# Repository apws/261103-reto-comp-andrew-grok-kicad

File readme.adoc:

= Z80 simple computer
:toc:
:toclevels: 2

The schematic is the rebuilt sheet. It opens, it uses stock KiCad 10.0.7 symbols, and the parts now sit inside the paper. The notes under `docs/` say how that was done.

The PCB file in this directory is not the posted board. That file would not open, and it is kept unchanged in `as-posted/`. The project board is a new KiCad 10 board. The signal tracks from the first routing attempt have been removed. What is on it now is the Eurocard outline, the parts placed on the top, four layers, and the inner ground and +5V planes. The DE9 plug hangs off the left edge. The screw-terminal holes hang off the right edge. There are no signal tracks. The STEP models are in `libs/kicad-packages3D-10.0.7/`, and the board names them with `${KIPRJMOD}`, the project directory.

The choices for this trial are in the plan. The sheet is A3, because the DIP-40 symbols do not fit A4. The board is a 160 by 100 mm Eurocard, four layers, a screw terminal for +5V, four M3 holes, and tracks written into the board file. FreeRouting was not used.

What is left:

. Route the signals in KiCad, one group of nets at a time. Not with the 0.25 mm grid script.
. The first proposed group is the two clocks and reset. See the note on Andrew's brief.

`tools/build_schematic.py` rewrites the schematic. If you move a part in KiCad and then run that script, the script wins. Either edit in KiCad and stop using the script, or change the script. Do not do both.

Read these first:

* link:docs/261103-what-went-wrong-and-how-to-do-it.adoc[Why the posted files are not a computer]
* link:docs/261103-a-guide-for-andrew.adoc[Doing the sheet one step at a time]
* link:docs/261104-00%20Chat%20transcript%20--%20fitting%20the%20symbols%20inside%20the%20frame.adoc[Fitting the symbols inside the frame]
* link:docs/261104-01%20Plan%20--%20placing%20and%20routing%20the%20board.adoc[Plan for placing and routing the board]
* link:docs/261104-02%20Chat%20transcript%20--%20the%20board%20plan%20and%20the%20public%20repo.adoc[The board plan, and the public repository]
* link:docs/261105-22%20Placing%20the%20Eurocard%20and%20the%20first%20tracks.adoc[Placing the Eurocard, and the first tracks]
* link:docs/261105-22%20JLCPCB%20rules%20for%20this%20board.adoc[JLCPCB rules for this board]
* link:docs/261105-23%20Placement%20only,%20connectors%20facing%20out.adoc[Placement only, connectors facing out]
* link:docs/261105-23%203D%20models%20for%20the%20footprints.adoc[3D models for the footprints]
* link:docs/261106-12%20Screw%20terminal%20holes%20facing%20out.adoc[Screw terminal holes facing out]
* link:docs/261106-12%20Capacitors%20beside%20the%20power%20pins.adoc[Capacitors beside the power pins]
* link:docs/261106-12%20MAX232%20beside%20the%20DE9.adoc[MAX232 beside the DE9]
* link:docs/261106-12%20Andrew's%20design%20brief.adoc[Andrew's design brief]
* link:docs/261106-12%20Where%20Andrew's%20brief%20meets%20this%20board.adoc[Where Andrew's brief meets this board]

== Previewing these notes

For a formatted view in Chrome or Chromium, install
https://chromewebstore.google.com/detail/asciidoctorjs-live-previe/iaalpfgpbocpdfblpnhhgllgbdbchmia[Asciidoctor.js Live Preview].
Enable *Allow access to file URLs* on the extension's details page, then open a local `.adoc` file.
The https://docs.asciidoctor.org/browser-extension/install/[installation notes] also mention Edge. Edge has not been tried here.

The two files in this directory are the Mixworx preview style used by the other local projects. Select them in the extension options:

* link:asciidoctorjs-crx-mixworx.css[asciidoctorjs-crx-mixworx.css]: stylesheet for type, headings, tables, code, and print.
* link:asciidoctorjs-crx-mixworx.js[asciidoctorjs-crx-mixworx.js]: run this *after the document has been rendered*. It marks modifier keys, splits a heading at the first prose colon, and puts anchor positions back after rendering.

If the repository moves, or either file changes, select them again in the extension options.
GitHub itself still shows the normal colon in a heading. The line break is only in this local preview.

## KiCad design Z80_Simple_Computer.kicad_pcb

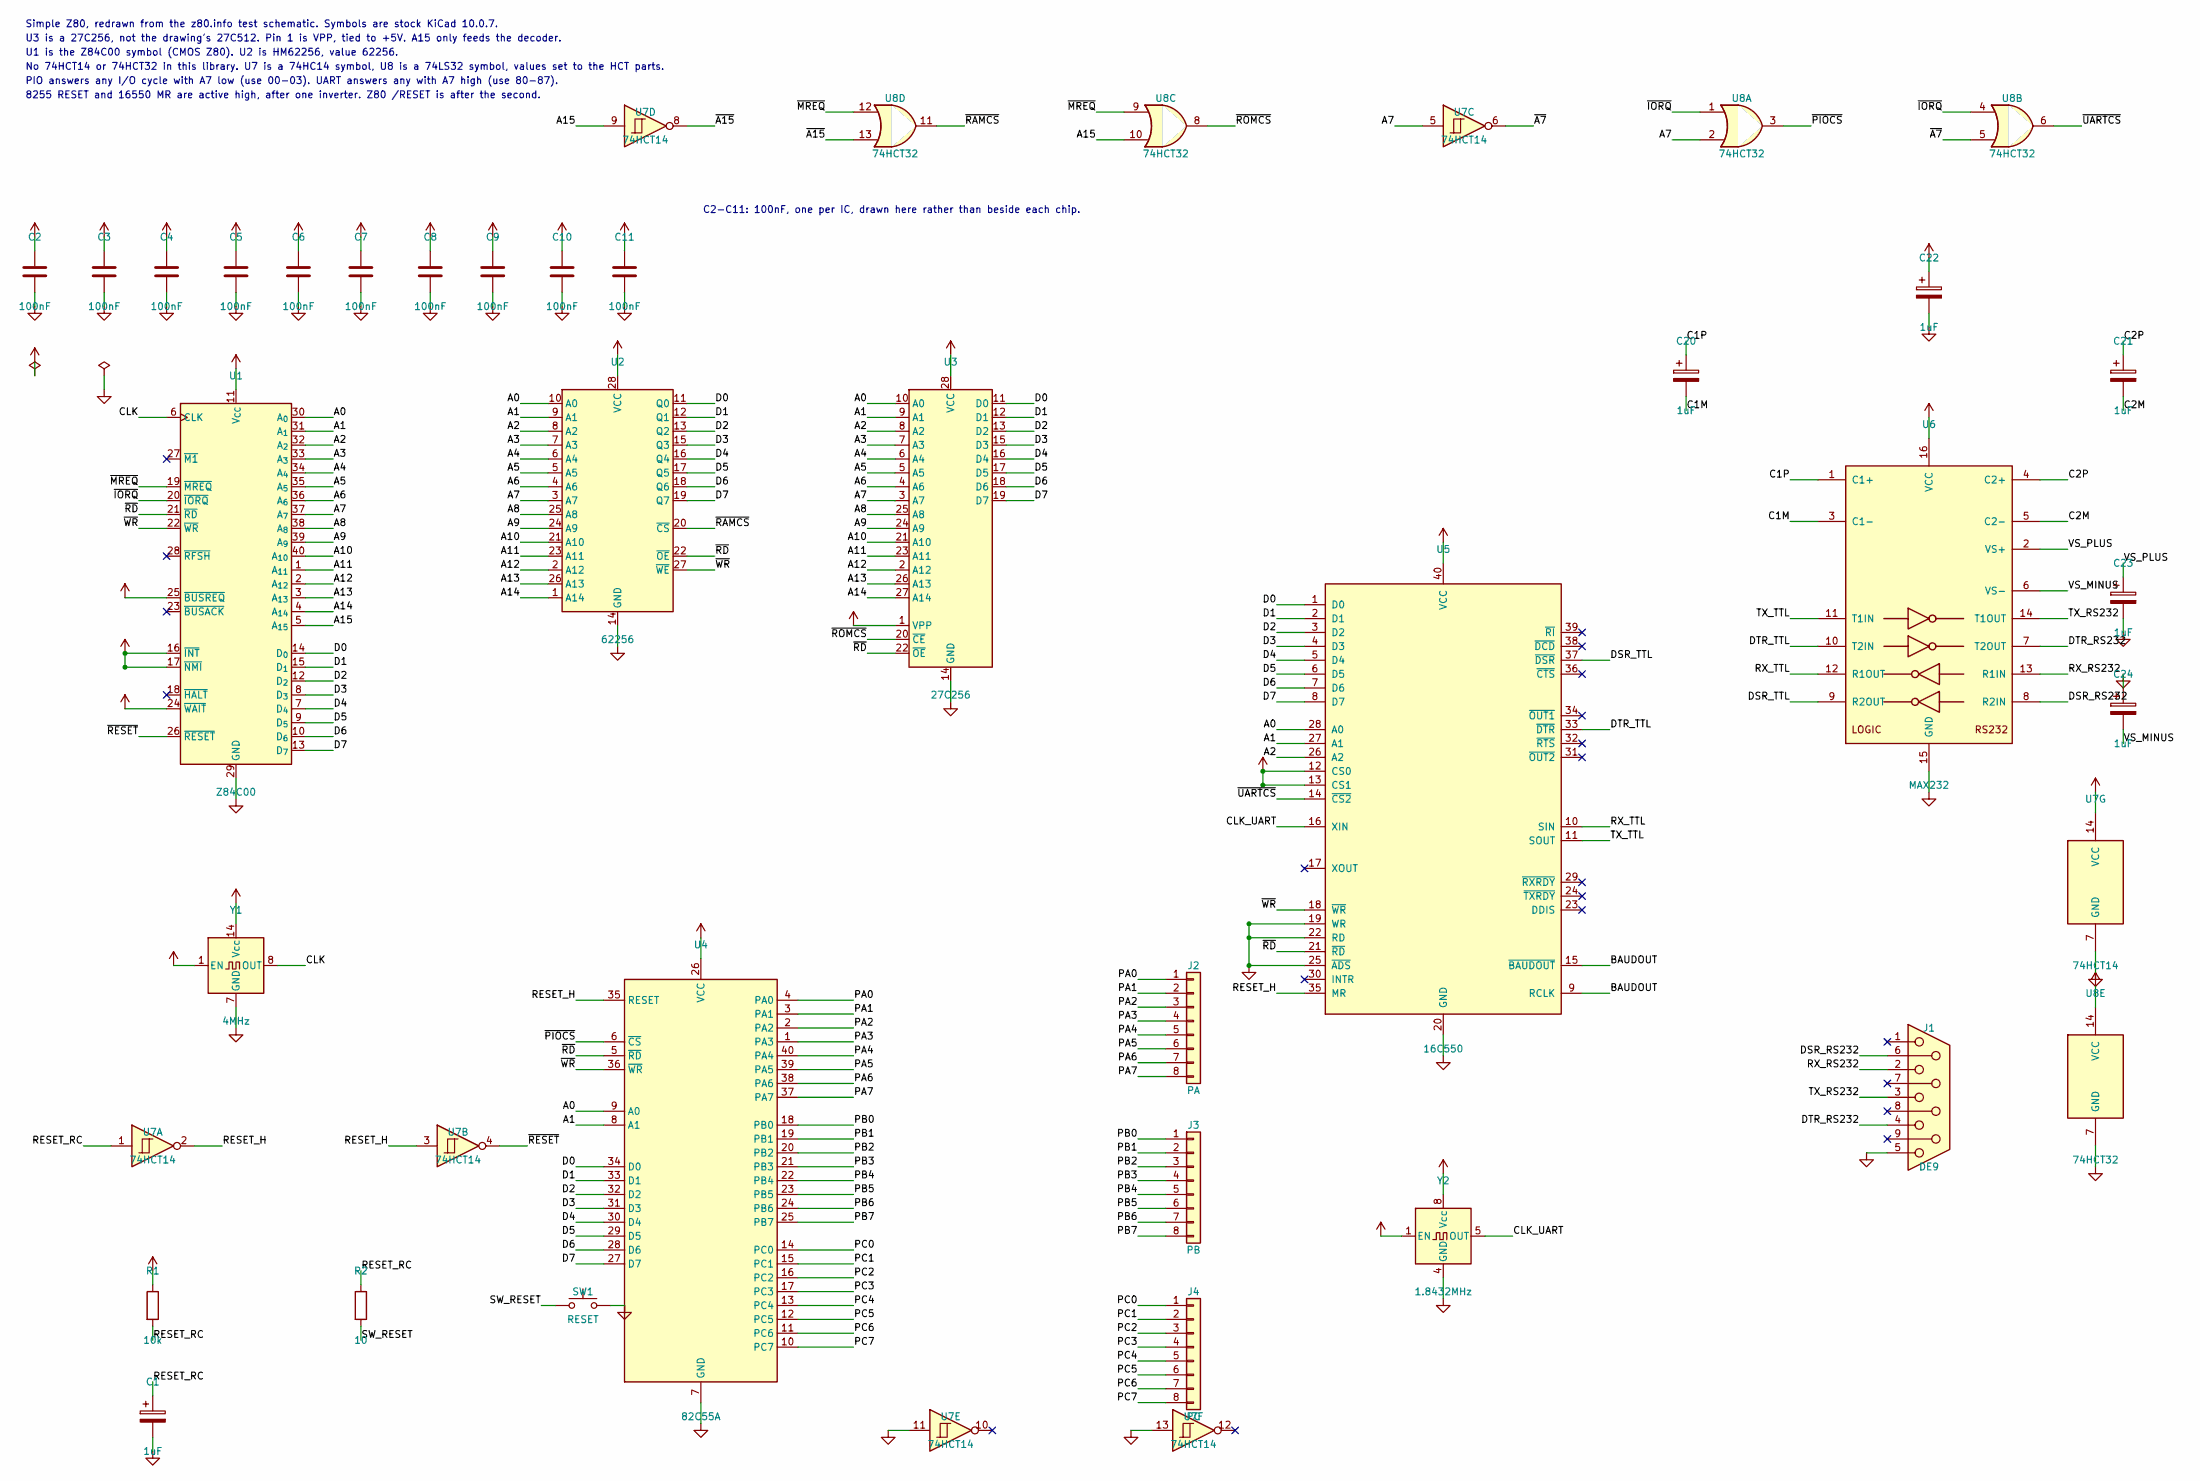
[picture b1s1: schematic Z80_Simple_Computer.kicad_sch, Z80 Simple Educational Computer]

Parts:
C1, C20, C21, C22, C23, C24: 1uF; CP_Radial_D5.0mm_P2.50mm
C2, C3, C4, C5, C6, C7, C8, C9, C10, C11: 100nF; C_Disc_D5.0mm_W2.5mm_P5.00mm
J1: DE9; DSUB-9_Socket_Horizontal_P2.77x2.84mm_EdgePinOffset4.94mm_H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
J2: PA; PinHeader_1x08_P2.54mm_Vertical
J3: PB; PinHeader_1x08_P2.54mm_Vertical
J4: PC; PinHeader_1x08_P2.54mm_Vertical
R1: 10k; R_Axial_DIN0207_L6.3mm_D2.5mm_P10.16mm_Horizontal
R2: 10; R_Axial_DIN0207_L6.3mm_D2.5mm_P10.16mm_Horizontal
SW1: RESET; SW_PUSH_6mm
U1: Z84C00; DIP-40_W15.24mm
U2: 62256; DIP-28_W15.24mm
U3: 27C256; DIP-28_W15.24mm
U4: 82C55A; DIP-40_W15.24mm
U5: 16C550; DIP-40_W15.24mm
U6: MAX232; DIP-16_W7.62mm
U7: 74HCT14; DIP-14_W7.62mm
U8: 74HCT32; DIP-14_W7.62mm
Y1: 4MHz; Oscillator_DIP-14
Y2: 1.8432MHz; Oscillator_DIP-8

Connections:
+5V: C2.1, C3.1, C4.1, C5.1, C6.1, C7.1, C8.1, C9.1, C10.1, C11.1, C22.1, R1.1, U1.11 (V_{CC}), U1.16 (~INT), U1.17 (~NMI), U1.24 (~WAIT), U1.25 (~BUSREQ), U2.28 (VCC), U3.1 (VPP), U3.28 (VCC), U4.26 (VCC), U5.12 (CS0), U5.13 (CS1), U5.40 (VCC), U6.16 (VCC), U7.14 (VCC), U8.14 (VCC), Y1.1 (EN), Y1.14 (Vcc), Y2.1 (EN), Y2.8 (Vcc); also elsewhere on the board
/A0: U1.30 (A_{0}), U2.10 (A0), U3.10 (A0), U4.9 (A0), U5.28 (A0)
/A1: U1.31 (A_{1}), U2.9 (A1), U3.9 (A1), U4.8 (A1), U5.27 (A1)
/A2: U1.32 (A_{2}), U2.8 (A2), U3.8 (A2), U5.26 (A2)
/A3: U1.33 (A_{3}), U2.7 (A3), U3.7 (A3)
/A4: U1.34 (A_{4}), U2.6 (A4), U3.6 (A4)
/A5: U1.35 (A_{5}), U2.5 (A5), U3.5 (A5)
/A6: U1.36 (A_{6}), U2.4 (A6), U3.4 (A6)
/A7: U1.37 (A_{7}), U2.3 (A7), U3.3 (A7), U7.5, U8.2
/A8: U1.38 (A_{8}), U2.25 (A8), U3.25 (A8)
/A9: U1.39 (A_{9}), U2.24 (A9), U3.24 (A9)
/A10: U1.40 (A_{10}), U2.21 (A10), U3.21 (A10)
/A11: U1.1 (A_{11}), U2.23 (A11), U3.23 (A11)
/A12: U1.2 (A_{12}), U2.2 (A12), U3.2 (A12)
/A13: U1.3 (A_{13}), U2.26 (A13), U3.26 (A13)
/A14: U1.4 (A_{14}), U2.1 (A14), U3.27 (A14)
/A15: U1.5 (A_{15}), U7.9, U8.10
/BAUDOUT: U5.9 (RCLK), U5.15 (~BAUDOUT)
/C1M: C20.2, U6.3 (C1-)
/C1P: C20.1, U6.1 (C1+)
/C2M: C21.2, U6.5 (C2-)
/C2P: C21.1, U6.4 (C2+)
/CLK: U1.6 (CLK), Y1.8 (OUT)
/CLK_UART: U5.16 (XIN), Y2.5 (OUT)
/D0: U1.14 (D_{0}), U2.11 (Q0), U3.11 (D0), U4.34 (D0), U5.1 (D0)
/D1: U1.15 (D_{1}), U2.12 (Q1), U3.12 (D1), U4.33 (D1), U5.2 (D1)
/D2: U1.12 (D_{2}), U2.13 (Q2), U3.13 (D2), U4.32 (D2), U5.3 (D2)
/D3: U1.8 (D_{3}), U2.15 (Q3), U3.15 (D3), U4.31 (D3), U5.4 (D3)
/D4: U1.7 (D_{4}), U2.16 (Q4), U3.16 (D4), U4.30 (D4), U5.5 (D4)
/D5: U1.9 (D_{5}), U2.17 (Q5), U3.17 (D5), U4.29 (D5), U5.6 (D5)
/D6: U1.10 (D_{6}), U2.18 (Q6), U3.18 (D6), U4.28 (D6), U5.7 (D6)
/D7: U1.13 (D_{7}), U2.19 (Q7), U3.19 (D7), U4.27 (D7), U5.8 (D7)
/DSR_RS232: J1.6, U6.8 (R2IN)
/DSR_TTL: U5.37 (~DSR), U6.9 (R2OUT)
/DTR_RS232: J1.4, U6.7 (T2OUT)
/DTR_TTL: U5.33 (~DTR), U6.10 (T2IN)
/PA0: J2.1, U4.4 (PA0)
/PA1: J2.2, U4.3 (PA1)
/PA2: J2.3, U4.2 (PA2)
/PA3: J2.4, U4.1 (PA3)
/PA4: J2.5, U4.40 (PA4)
/PA5: J2.6, U4.39 (PA5)
/PA6: J2.7, U4.38 (PA6)
/PA7: J2.8, U4.37 (PA7)
/PB0: J3.1, U4.18 (PB0)
/PB1: J3.2, U4.19 (PB1)
/PB2: J3.3, U4.20 (PB2)
/PB3: J3.4, U4.21 (PB3)
/PB4: J3.5, U4.22 (PB4)
/PB5: J3.6, U4.23 (PB5)
/PB6: J3.7, U4.24 (PB6)
/PB7: J3.8, U4.25 (PB7)
/PC0: J4.1, U4.14 (PC0)
/PC1: J4.2, U4.15 (PC1)
/PC2: J4.3, U4.16 (PC2)
/PC3: J4.4, U4.17 (PC3)
/PC4: J4.5, U4.13 (PC4)
/PC5: J4.6, U4.12 (PC5)
/PC6: J4.7, U4.11 (PC6)
/PC7: J4.8, U4.10 (PC7)
/RESET_H: U4.35 (RESET), U5.35 (MR), U7.2, U7.3
/RESET_RC: C1.1, R1.2, R2.1, U7.1
/RX_RS232: J1.2, U6.13 (R1IN)
/RX_TTL: U5.10 (SIN), U6.12 (R1OUT)
/SW_RESET: R2.2, SW1.1
/TX_RS232: J1.3, U6.14 (T1OUT)
/TX_TTL: U5.11 (SOUT), U6.11 (T1IN)
/VS_MINUS: C24.2, U6.6 (VS-)
/VS_PLUS: C23.1, U6.2 (VS+)
/~A7: U7.6, U8.5
/~A15: U7.8, U8.13
/~IORQ: U1.20 (~IORQ), U8.1, U8.4
/~MREQ: U1.19 (~MREQ), U8.9, U8.12
/~PIOCS: U4.6 (~CS), U8.3
/~RAMCS: U2.20 (~CS), U8.11
/~RD: U1.21 (~RD), U2.22 (~OE), U3.22 (~OE), U4.5 (~RD), U5.21 (~RD)
/~RESET: U1.26 (~RESET), U7.4
/~ROMCS: U3.20 (~CE), U8.8
/~UARTCS: U5.14 (~CS2), U8.6
/~WR: U1.22 (~WR), U2.27 (~WE), U4.36 (~WR), U5.18 (~WR)
GND: C1.2, C2.2, C3.2, C4.2, C5.2, C6.2, C7.2, C8.2, C9.2, C10.2, C11.2, C22.2, C23.2, C24.1, J1.5, SW1.2, U1.29 (GND), U2.14 (GND), U3.14 (GND), U4.7 (GND), U5.19 (WR), U5.20 (GND), U5.22 (RD), U5.25 (~ADS), U6.15 (GND), U7.7 (GND), U7.11, U7.13, U8.7 (GND), Y1.7 (GND), Y2.4 (GND); also elsewhere on the board

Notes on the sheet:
Simple Z80, redrawn from the z80.info test schematic. Symbols are stock KiCad 10.0.7.
U3 is a 27C256, not the drawing's 27C512. Pin 1 is VPP, tied to +5V. A15 only feeds the decoder.
U1 is the Z84C00 symbol (CMOS Z80). U2 is HM62256, value 62256.
No 74HCT14 or 74HCT32 in this library. U7 is a 74HC14 symbol, U8 is a 74LS32 symbol, values set to the HCT parts.
PIO answers any I/O cycle with A7 low (use 00-03). UART answers any with A7 high (use 80-87).
8255 RESET and 16550 MR are active high, after one inverter. Z80 /RESET is after the second.
C2-C11: 100nF, one per IC, drawn here rather than beside each chip.

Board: 4 copper layers, 38 parts (0 on the bottom side), 81 nets, no tracks yet.

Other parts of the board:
H1, H2, H3, H4: M3; MountingHole_3.2mm_M3
J5: PWR; TerminalBlock_Phoenix_MKDS-1,5-2-5.08_1x02_P5.08mm_Horizont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

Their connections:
+5V: J5.1; also elsewhere on the board
GND: J5.2; also elsewhere on the board

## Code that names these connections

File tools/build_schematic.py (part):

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        sh.label_named("U2", f"A{bit}", f"A{bit}")
    for bit in range(8):
        sh.label_named("U2", f"Q{bit}", f"D{bit}")
    sh.label_named("U2", "~{CS}", "~{RAMCS}")
    sh.label_named("U2", "~{OE}", "~{RD}")
    sh.label_named("U2", "~{WE}", "~{WR}")
    sh.power_on("U2", "VCC", "+5V")
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        sh.label_named("U3", f"A{bit}", f"A{bit}")
    for bit in range(8):
        sh.label_named("U3", f"D{bit}", f"D{bit}")
    sh.label_named("U3", "~{CE}", "~{ROMCS}")
    sh.label_named("U3", "~{OE}", "~{RD}")
    sh.power_on("U3", "VPP", "+5V", length=7.62)
    sh.power_on("U3", "VCC", "+5V")
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    sh.label_named("U4", "A1", "A1")
    sh.label_named("U4", "~{RD}", "~{RD}")
    sh.label_named("U4", "~{WR}", "~{WR}")
    sh.label_named("U4", "~{CS}", "~{PIOCS}")
    sh.label_named("U4", "RESET", "RESET_H")
    sh.power_on("U4", "VCC", "+5V")
    sh.power_on("U4", "GND", "GND")
    # The GIF leaves the PIO ports open. A header gives each label a second pin
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    # The helper above already wired C22 to +5V/GND. That cap is still a
    # valid 1uF across the rail; use three more for the pump and V-.
    # Rewire pump pins with labels matching C20/C21, and add V+ / V- caps.
    sh.label_named("U6", "C1+", "C1P")
    sh.label_named("U6", "C1-", "C1M")
    sh.label_named("U6", "C2+", "C2P")
    sh.label_named("U6", "C2-", "C2M")
    sh.label_named("U6", "VS+", "VS_PLUS")
    sh.label_named("U6", "VS-", "VS_MINUS")
    polarized("C23", 400, 118, "VS_PLUS", "GND")
    # V- cap: positive at GND, negative at VS-.
    polarized("C24", 400, 138, "GND", "VS_MINUS")
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    sh.power_on("Y1", "EN", "+5V")
    sh.power_on("Y1", "GND", "GND")
    sh.power_on("Y1", "Vcc", "+5V")
    sh.label_named("Y2", "OUT", "CLK_UART")
    sh.power_on("Y2", "EN", "+5V")
    sh.power_on("Y2", "GND", "GND")
    sh.power_on("Y2", "Vcc", "+5V")
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    # U7D: A15 -> /A15. U8D: /MREQ OR /A15 = /RAMCS. U8C: /MREQ OR A15 = /ROMCS.
    sh.label_pin("U7", "9", "A15", unit=4)
    sh.label_pin("U7", "8", "~{A15}", unit=4)
    sh.label_pin("U8", "12", "~{MREQ}", unit=4)
    sh.label_pin("U8", "13", "~{A15}", unit=4)
    sh.label_pin("U8", "11", "~{RAMCS}", unit=4)
    sh.label_pin("U8", "9", "~{MREQ}", unit=3)
    sh.label_pin("U8", "10", "A15", unit=3)
    sh.label_pin("U8", "8", "~{ROMCS}", unit=3)
    # U7C: A7 -> /A7. U8A: /IORQ OR A7 = /PIOCS (A7 low). U8B: /IORQ OR /A7 = /UARTCS.
    sh.label_pin("U7", "5", "A7", unit=3)
    sh.label_pin("U7", "6", "~{A7}", unit=3)
    sh.label_pin("U8", "1", "~{IORQ}", unit=1)
    sh.label_pin("U8", "2", "A7", unit=1)
    sh.label_pin("U8", "3", "~{PIOCS}", unit=1)
    sh.label_pin("U8", "4", "~{IORQ}", unit=2)
    sh.label_pin("U8", "5", "~{A7}", unit=2)
    sh.label_pin("U8", "6", "~{UARTCS}", unit=2)

    # --- reset. Two Schmitt inversions. Active-high parts take the first. ---
    sh.place("R1", "Device:R", "10k", 40, 248, 1, FP_R, pins["r"])
    sh.place("R2", "Device:R", "10", 78, 248, 1, FP_R, pins["r"])
    sh.place("C1", "Device:C_Polarized", "1uF", 40, 268, 1, FP_CP, pins["cp"])
    sh.place("SW1", "Switch:SW_Push", "RESET", 118, 248, 1, FP_SW, pins["sw"])
    # R1 pin 1 top toward +5V, pin 2 bottom toward RESET_RC
    sh.power_on("R1", "1", "+5V", length=2.54)
    sh.label_pin("R1", "2", "RESET_RC", length=2.54)
    sh.label_pin("C1", "1", "RESET_RC", length=2.54)
    sh.power_on("C1", "2", "GND", length=2.54)
    sh.label_pin("R2", "1", "RESET_RC", length=2.54)
    sh.label_pin("R2", "2", "SW_RESET", length=2.54)
    sh.label_pin("SW1", "1", "SW_RESET", length=2.54)
    sh.power_on("SW1", "2", "GND", length=2.54)
    sh.label_pin("U7", "1", "RESET_RC", unit=1)
    sh.label_pin("U7", "2", "RESET_H", unit=1)
    sh.label_pin("U7", "3", "RESET_H", unit=2)
    sh.label_pin("U7", "4", "~{RESET}", unit=2)

    # spare inverters: input held, output unused
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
